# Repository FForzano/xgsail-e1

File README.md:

# XGSail-E1

E1 device firmware and hardware for [XGSail](https://github.com/FForzano/xgsail) —
an ESP32 sailboat tracker: GNSS + IMU + wind + pressure logging, an
ESP-NOW peer mesh for live fleet position sharing and on-course-side
(OCS) race-start detection, and uploads over the XGSail device
protocol — direct over WiFi, or relayed over BLE by the owner's phone
when WiFi isn't available.

> **xgsail-e1 is derived from `sailframes/core`**, the upstream hardware/
> firmware project. It is not a GitHub fork of that repository (see
> "Relationship to SailFrames Core" below for why, and where this
> content actually came from) — it's a from-scratch export of the E1
> device's firmware and hardware, reorganized into per-responsibility
> modules and stripped down to E1 only.

## What xgsail-e1 Is

xgsail-e1 is the firmware and PCB design for one specific device: **E1**,
an ESP32-based fleet tracker.

It provides:

- Firmware (`firmware/sailframes_edge/`) — GNSS/IMU/wind/pressure sensor
  reads, SD-card session logging, an ESP-NOW peer mesh with on-course-side
  (OCS) race-start detection, the XGSail device-protocol claim/upload flow
  (direct over WiFi and a BLE GATT relay for when WiFi isn't available),
  and a serial/telnet console.
- Hardware (`hardware/`) — the KiCad 8+ schematic, PCB layout, Gerbers,
  and BOM for the E1 board.
- Documentation (`docs/`) — the firmware's internal architecture, GNSS/RTK
  configuration and PPK post-processing workflow, and the current battery/
  display/power hardware.

The device talks to the XGSail backend through the hardware-agnostic
ingestion contract documented in xgsail's `docs/device-protocol.md`
(device claim, `DeviceKey` auth, presigned session uploads, and the BLE
relay contract for WiFi-less operation) — this repo implements that
contract, it doesn't redefine it.

## What xgsail-e1 Is Not

xgsail-e1 is **not** the software platform — users, roles, clubs, the
ingestion API, analytics, or the web/native apps. That's
[XGSail](https://github.com/FForzano/xgsail).

It is also not the general SailFrames Core hardware project: other
device families from that upstream (a Raspberry-Pi-based "Edge-S" unit,
a sealed-enclosure successor board, and a standalone BLE wind-sensor
accessory) are out of scope here on purpose — this repository is E1 only.

## Relationship to SailFrames Core

XGSail's own `xgsail` repository is itself a GitHub-level fork of
`sailframes/core`, the upstream hardware+software monorepo — before its
software layer was redesigned into what is now XGSail, that repository's
history contained `edge-e/` (the E1 device: this firmware + hardware),
`edge-b/` (a later, different hardware platform), and `edge-s/` (the
Raspberry-Pi device), alongside the cloud-side code that became XGSail's
backend/frontend/workers.

xgsail-e1 is an export of `edge-e/` from that history: the firmware and
hardware for E1 specifically, with the other device families and the
now-superseded cloud-side code left out, and the firmware's `#ifdef`s for
the non-E1 hardware variant removed rather than carried forward as dead
code. It is not a `git fork` of `sailframes/core` (GitHub only allows one
fork per repo per account, and that slot is already used by `xgsail`) —
its origin is recorded here in `docs/firmware-architecture.md` and this
README instead of in GitHub's fork metadata.

License: Apache 2.0, same as upstream and same as xgsail — no relicensing.

## Display

3.5" TFT dashboard, three nav layouts cycled live (console or BLE), plus
two race-committee-only panels for fleet OCS detection:

<br>D2 — nav + wind (default) &nbsp;·&nbsp; RC panel — live OCS per boat

See `docs/hardware.md`'s Display section for all three nav modes and
both RC panels.

## Quick start

### Firmware

```bash
cd firmware/sailframes_edge
# Open in Arduino IDE, or build with PlatformIO
```

See `firmware/README.md` for board settings, library dependencies, pin
assignments, SD card setup, and the full serial/telnet console command
reference.

### Hardware (KiCad)

```bash
cd hardware
kicad kicad_sailframes-e1.kicad_pro
```

## Repository layout

`firmware/sailframes_edge/` (main sketch, one file/pair per
responsibility — see `CLAUDE.md` for the full module map) ·
`firmware/{e1_sd_card,i2c_scan,sailframes_e1_diag}/` (sample SD contents
and standalone bring-up sketches) · `hardware/` (KiCad project + fab
outputs) · `docs/{firmware-architecture,gnss-rtk,hardware}.md`.

## License

Apache 2.0.

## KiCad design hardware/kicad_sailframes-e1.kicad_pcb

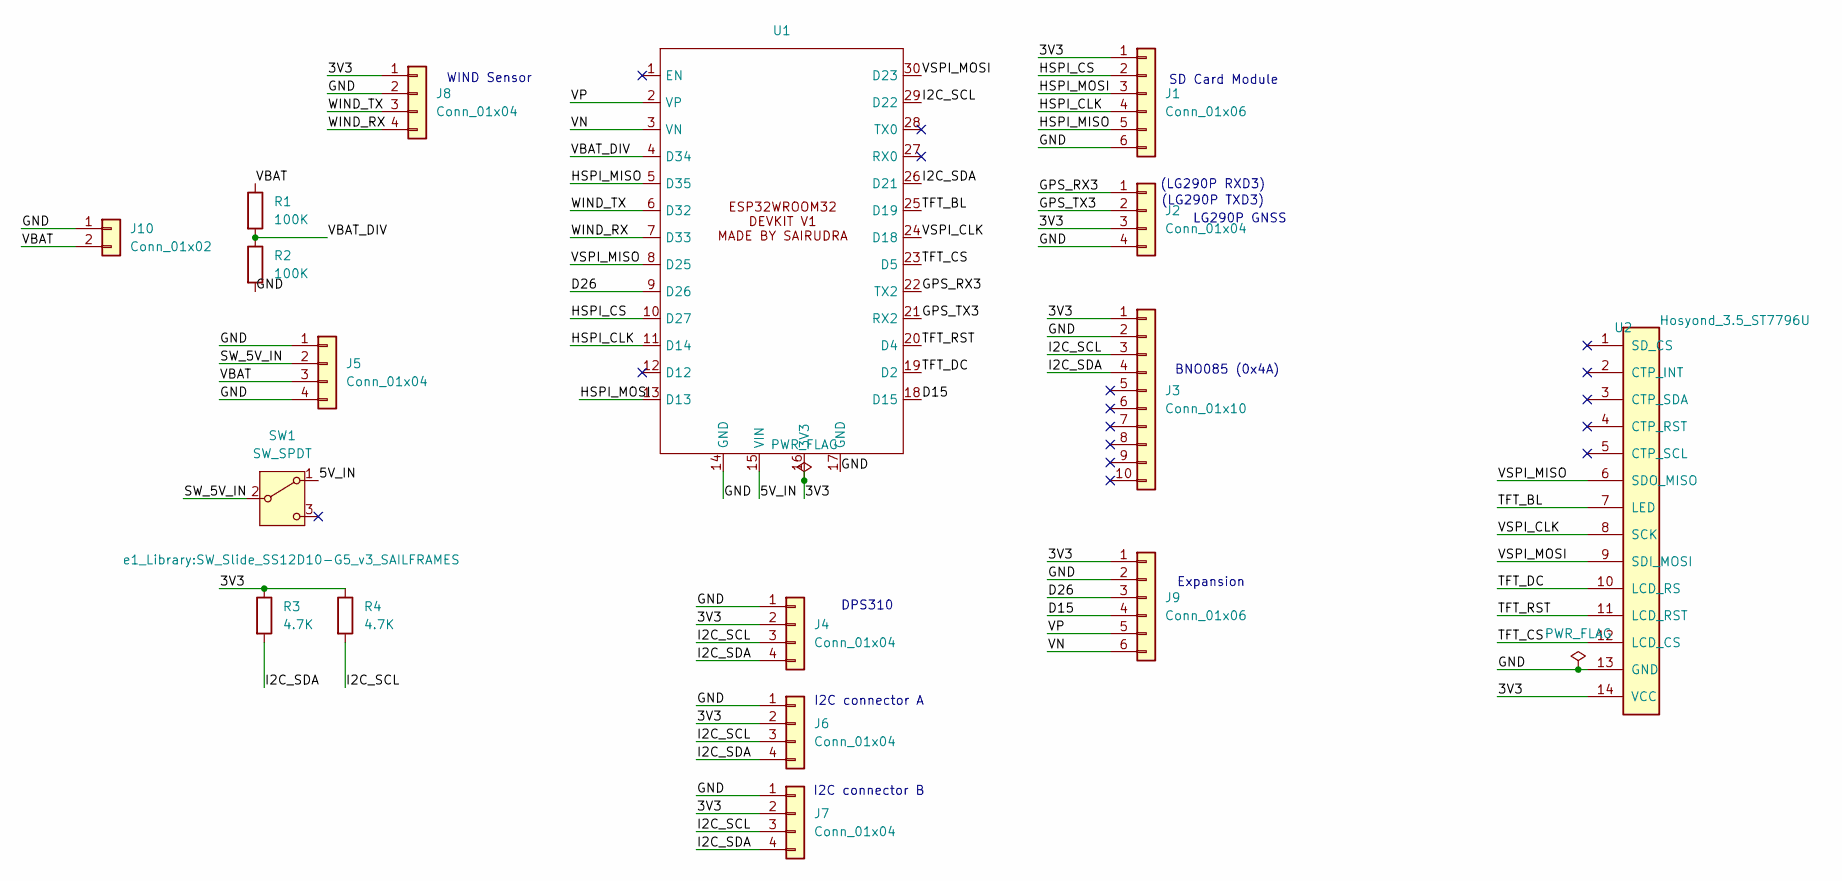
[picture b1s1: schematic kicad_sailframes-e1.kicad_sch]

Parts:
J1: Conn_01x06; SD_CARD
J2, J4, J5, J6, J7, J8: Conn_01x04; PinHeader_1x04_P2.54mm_Vertical
J3: Conn_01x10; PinHeader_1x10_P2.54mm_Vertical
J9: Conn_01x06; PinHeader_1x06_P2.54mm_Vertical
J10: Conn_01x02; JST_PH_S2B-PH-K_1x02_P2.00mm_Horizontal
R1, R2: 100K; R_0805_2012Metric
R3, R4: 4.7K; R_0805_2012Metric
SW1: SW_SPDT; SW_Slide_SS12D10-G5_v3_SAILFRAMES
U1: ESP32DEVIKITV1
U2: Hosyond_3.5_ST7796U; PinHeader_1x14_P2.54mm_Vertical

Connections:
/3V3: J1.1, J2.3, J3.1, J4.2, J6.2, J7.2, J8.1, J9.1, R3.1, R4.1, U1.16 (3V3), U2.14 (VCC)
/5V_IN: SW1.1 (A), U1.15 (VIN)
/D15: J9.4, U1.18 (D15)
/D26: J9.3, U1.9 (D26)
/GND: J1.6, J2.4, J3.2, J4.1, J5.1, J5.4, J6.1, J7.1, J8.2, J9.2, J10.1, R2.2, U1.14 (GND), U1.17 (GND), U2.13 (GND)
/GPS_RX3: J2.1, U1.22 (TX2)
/GPS_TX3: J2.2, U1.21 (RX2)
/HSPI_CLK: J1.4, U1.11 (D14)
/HSPI_CS: J1.2, U1.10 (D27)
/HSPI_MISO: J1.5, U1.5 (D35)
/HSPI_MOSI: J1.3, U1.13 (D13)
/I2C_SCL: J3.3, J4.3, J6.3, J7.3, R4.2, U1.29 (D22)
/I2C_SDA: J3.4, J4.4, J6.4, J7.4, R3.2, U1.26 (D21)
/SW_5V_IN: J5.2, SW1.2 (B)
/TFT_BL: U1.25 (D19), U2.7 (LED)
/TFT_CS: U1.23 (D5), U2.12 (LCD_CS)
/TFT_DC: U1.19 (D2), U2.10 (LCD_RS)
/TFT_RST: U1.20 (D4), U2.11 (LCD_RST)
/VBAT: J5.3, J10.2, R1.1
/VBAT_DIV: R1.2, R2.1, U1.4 (D34)
/VN: J9.6, U1.3 (VN)
/VP: J9.5, U1.2 (VP)
/VSPI_CLK: U1.24 (D18), U2.8 (SCK)
/VSPI_MISO: U1.8 (D25), U2.6 (SDO_MISO)
/VSPI_MOSI: U1.30 (D23), U2.9 (SDI_MOSI)
/WIND_RX: J8.4, U1.7 (D33)
/WIND_TX: J8.3, U1.6 (D32)

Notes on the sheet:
Expansion
LG290P GNSS
(LG290P RXD3)
(LG290P TXD3)
SD Card Module
BNO085 (0x4A)
WIND Sensor
I2C connector A
DPS310
I2C connector B

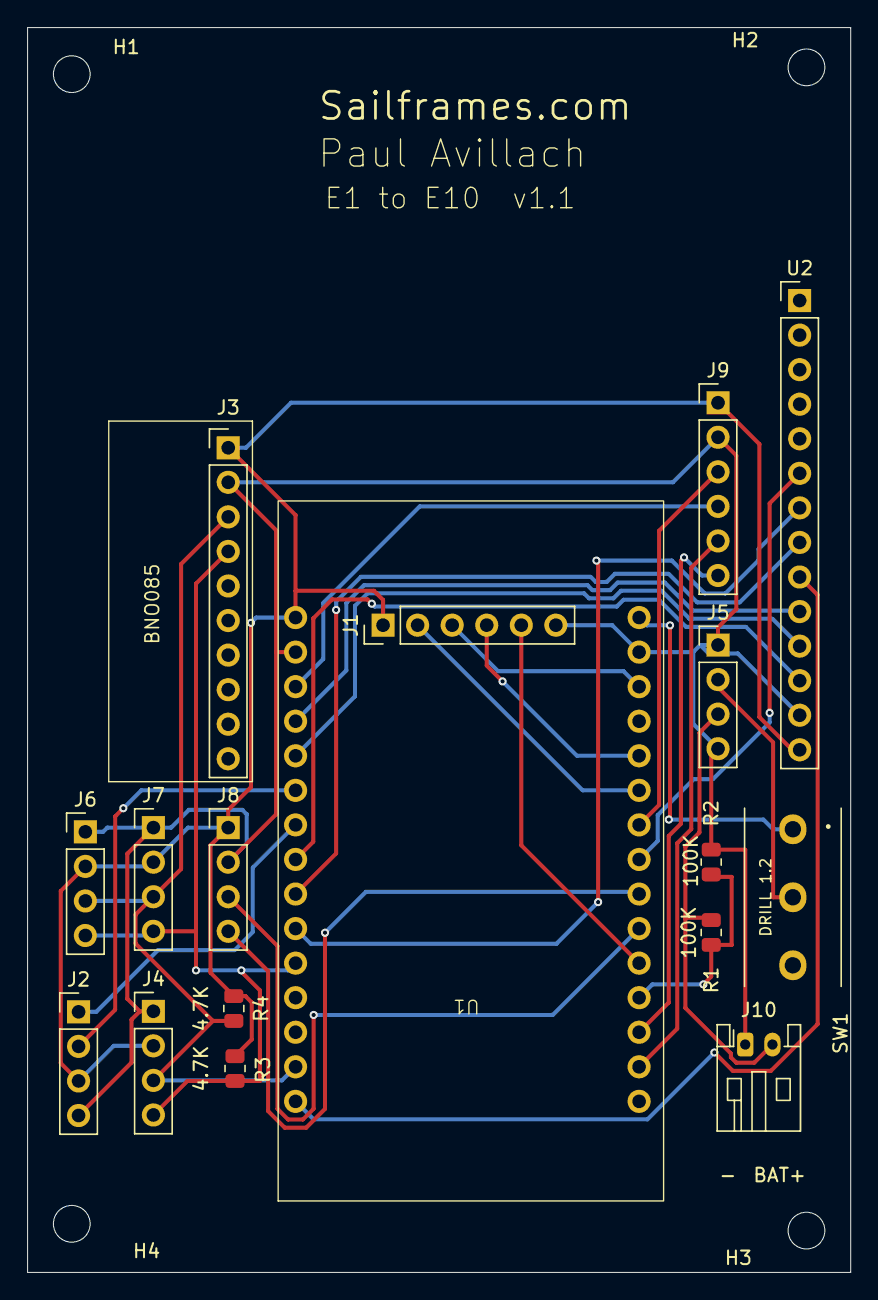
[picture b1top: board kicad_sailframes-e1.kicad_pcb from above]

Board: 2 copper layers, 60.5 x 91.5 mm, 21 parts (0 on the bottom side), 27 nets.

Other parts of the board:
H1, H2, H3, H4: MountingHole_2.7mm_M2.5

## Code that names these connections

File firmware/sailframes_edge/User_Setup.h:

// ============================================================
// SailFrames E1 — TFT_eSPI User_Setup.h
//   3.5" IPS ST7796U, 480x320, SPI
//
// #define USER_SETUP_LOADED is set here so TFT_eSPI uses THIS file
// (it is #included by display.h before <TFT_eSPI.h>).
// ============================================================

#define USER_SETUP_LOADED

#define ST7796_DRIVER
#define TFT_WIDTH  320
#define TFT_HEIGHT 480
#define TFT_MISO  25   // Swapped with BL to match soldered E1 wiring
#define TFT_BL    19   // Swapped with MISO to match soldered E1 wiring
#define TFT_BACKLIGHT_ON HIGH

// ESP32 SPI pin assignments (common to both displays)
#define TFT_MOSI  23
#define TFT_SCLK  18
#define TFT_CS     5
#define TFT_DC     2
#define TFT_RST    4

// SPI frequency — 40MHz is safe for both ST7796 and ILI9341
#define SPI_FREQUENCY       40000000
#define SPI_READ_FREQUENCY  20000000
#define SPI_TOUCH_FREQUENCY  2500000

// Enable SPI transactions for proper bus arbitration with SD card
#define SUPPORT_TRANSACTIONS

// Fonts — load only what's needed to save flash
#define LOAD_GLCD    // 8px font
#define LOAD_FONT2   // 16px font
#define LOAD_FONT4   // 26px font
#define LOAD_FONT6   // 48px numeric font
#define LOAD_FONT7   // 48px 7-segment font
#define LOAD_FONT8   // 75px numeric font
#define LOAD_GFXFF   // FreeFonts support
#define SMOOTH_FONT
